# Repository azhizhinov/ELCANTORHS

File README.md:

## El Cantor HS

The El Cantor HS keyboard is a 44 key diodeless split keyboard with support for hotswap sockets, designed with simplicity in mind. It is based on the popular [cantor](https://github.com/diepala/cantor), which is inspired on the popular [corne](https://github.com/foostan/crkbd), [ferris](https://github.com/pierrechevalier83/ferris) and [sweep](https://github.com/davidphilipbarr/Sweep) keyboards, aiming to provide a more ergonomic (stronger column stagger) corne-like layout with a simple, easy to assemble and cheap design.
This is a WIP, you can follow the [Cantor's build guide](https://github.com/diepala/cantor/blob/main/doc/build_guide.md), as it is quite similar!

## Thanks
Big thanks to [@Excellenze11](https://github.com/Excellenze11) for ideas, cooperation and tests.

## Parts
As for the parts list, you will need:
- 2x PCB (The left and right half are the same)
- 44 Chocv1 Keys
- 44 Chocv1 Keycaps
- 44 Hotswap sockets for Chocv1 (optional)
- 2x TRRS jacks (PJ-320A)
- 2x Blackpill microcontrollers (STM32F401CC)

## Gerbers
You can find the Gerber files needed to order the PCB on the `Gerbers` directory. Look for the .zip of whatever version you would like!

## Firmware
Firmware for this keyboard is in the QMK tree. You can find sources in this [path](https://github.com/qmk/qmk_firmware/tree/master/keyboards/elcantorhs). You can see/change the layout [here](https://config.qmk.fm/#/elcantorhs/LAYOUT).

## Attention
I'm a hobbyist/amateur at best. So there may be things that aren't optimized. So if you decide to use this, then please be advised that I'm not providing any sort of liability and you should exercise some caution. Use these file for your own risk. Thanks Sebastian Stumpf for this text.

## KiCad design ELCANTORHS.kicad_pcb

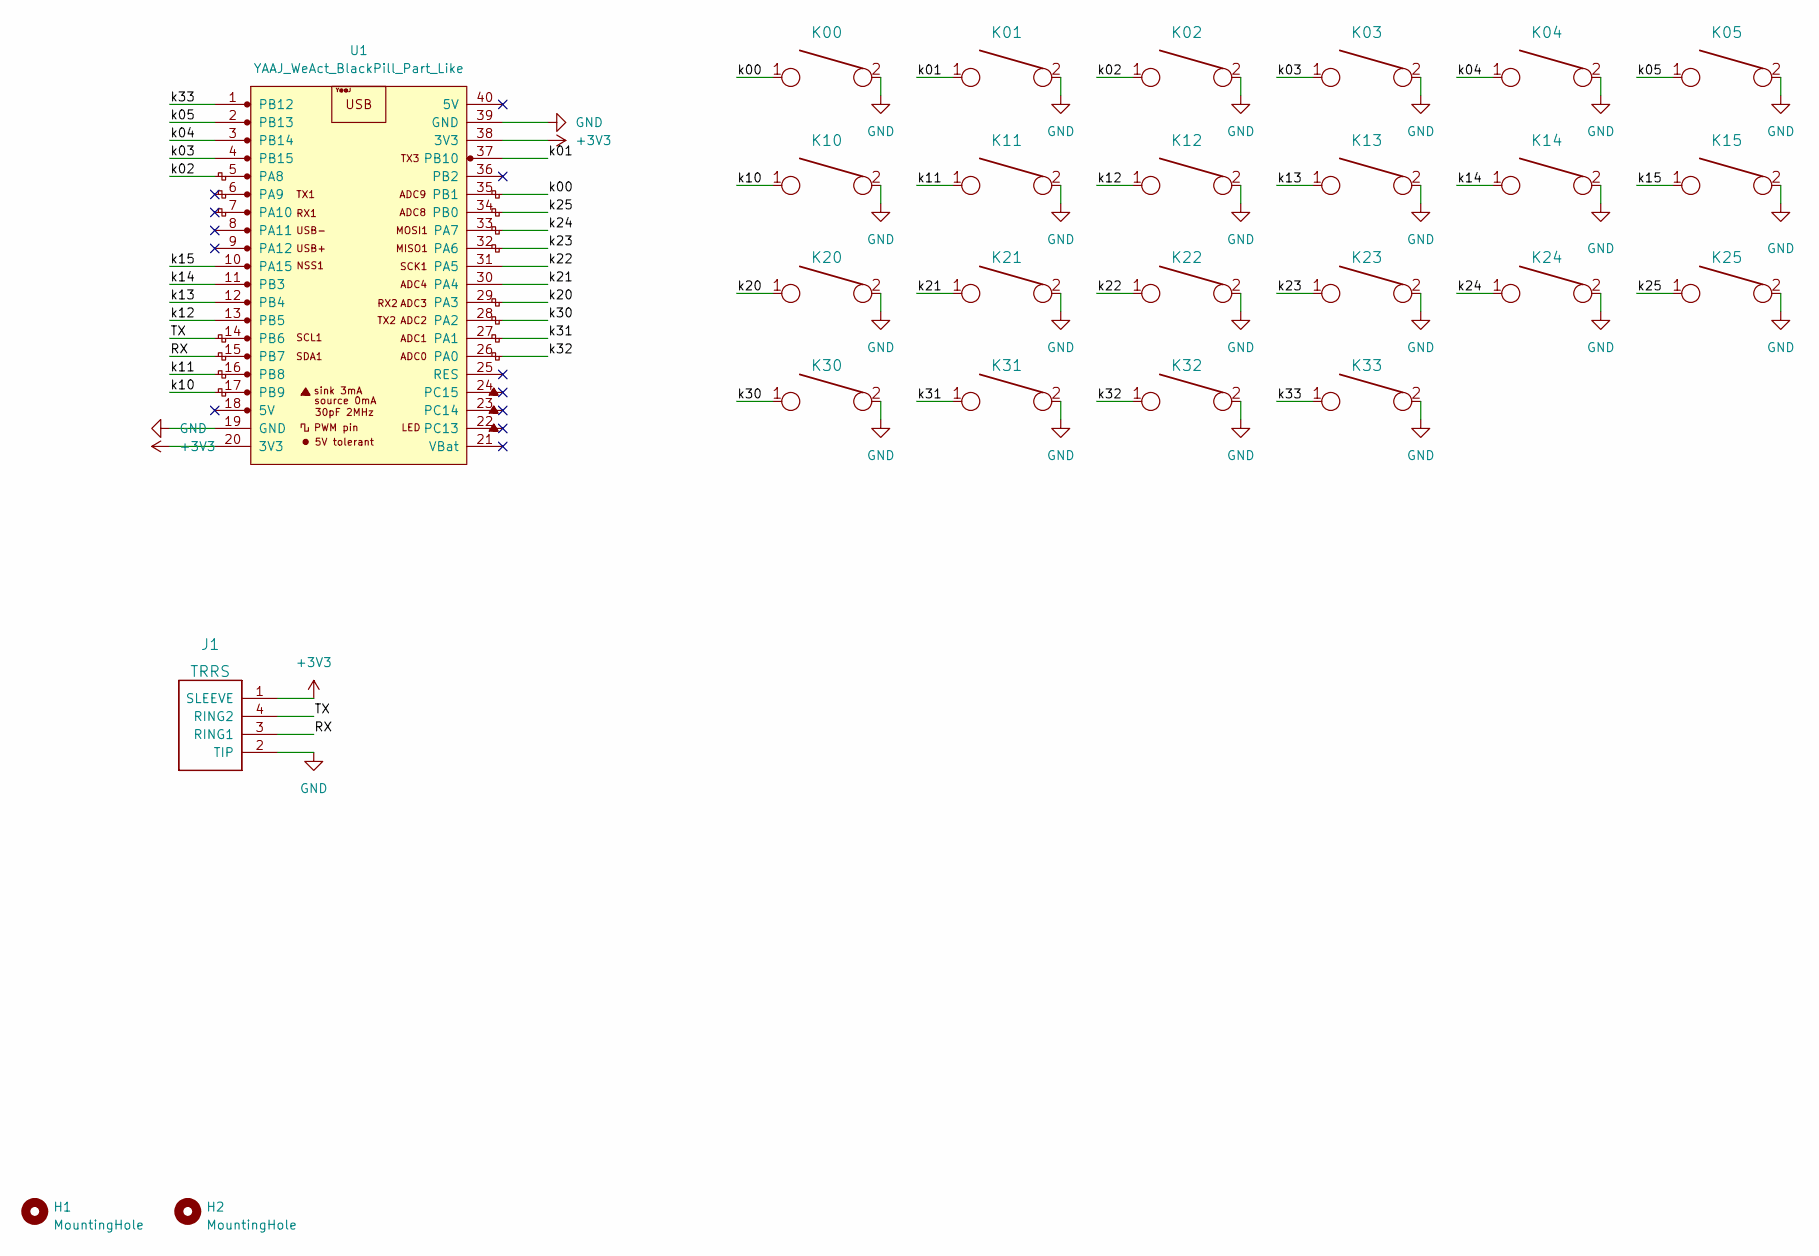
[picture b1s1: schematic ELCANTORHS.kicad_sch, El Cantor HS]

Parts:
H1, H2: MountingHole; breakaway-mousebites
J1: TRRS; TRRS-PJ-320A
K00, K01, K02, K03, K04, K05, K10, K11, K12, K13, K14, K15, K20, K21, K22, K23, K24, K25, K30, K31, K32, K33: KEYSW; Kailh_socket_PG1350_optional_reversible
U1: YAAJ_WeAct_BlackPill_Part_Like; YAAJ_WeAct_BlackPill_2

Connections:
+3V3: J1.1 (SLEEVE), U1.20 (3V3), U1.38 (3V3)
/RX: J1.3 (RING1), U1.15 (PB7)
/TX: J1.4 (RING2), U1.14 (PB6)
/k00: K00.1, U1.35 (PB1)
/k01: K01.1, U1.37 (PB10)
/k02: K02.1, U1.5 (PA8)
/k03: K03.1, U1.4 (PB15)
/k04: K04.1, U1.3 (PB14)
/k05: K05.1, U1.2 (PB13)
/k10: K10.1, U1.17 (PB9)
/k11: K11.1, U1.16 (PB8)
/k12: K12.1, U1.13 (PB5)
/k13: K13.1, U1.12 (PB4)
/k14: K14.1, U1.11 (PB3)
/k15: K15.1, U1.10 (PA15)
/k20: K20.1, U1.29 (PA3)
/k21: K21.1, U1.30 (PA4)
/k22: K22.1, U1.31 (PA5)
/k23: K23.1, U1.32 (PA6)
/k24: K24.1, U1.33 (PA7)
/k25: K25.1, U1.34 (PB0)
/k30: K30.1, U1.28 (PA2)
/k31: K31.1, U1.27 (PA1)
/k32: K32.1, U1.26 (PA0)
/k33: K33.1, U1.1 (PB12)
GND: J1.2 (TIP), K00.2, K01.2, K02.2, K03.2, K04.2, K05.2, K10.2, K11.2, K12.2, K13.2, K14.2, K15.2, K20.2, K21.2, K22.2, K23.2, K24.2, K25.2, K30.2, K31.2, K32.2, K33.2, U1.19 (GND), U1.39 (GND)

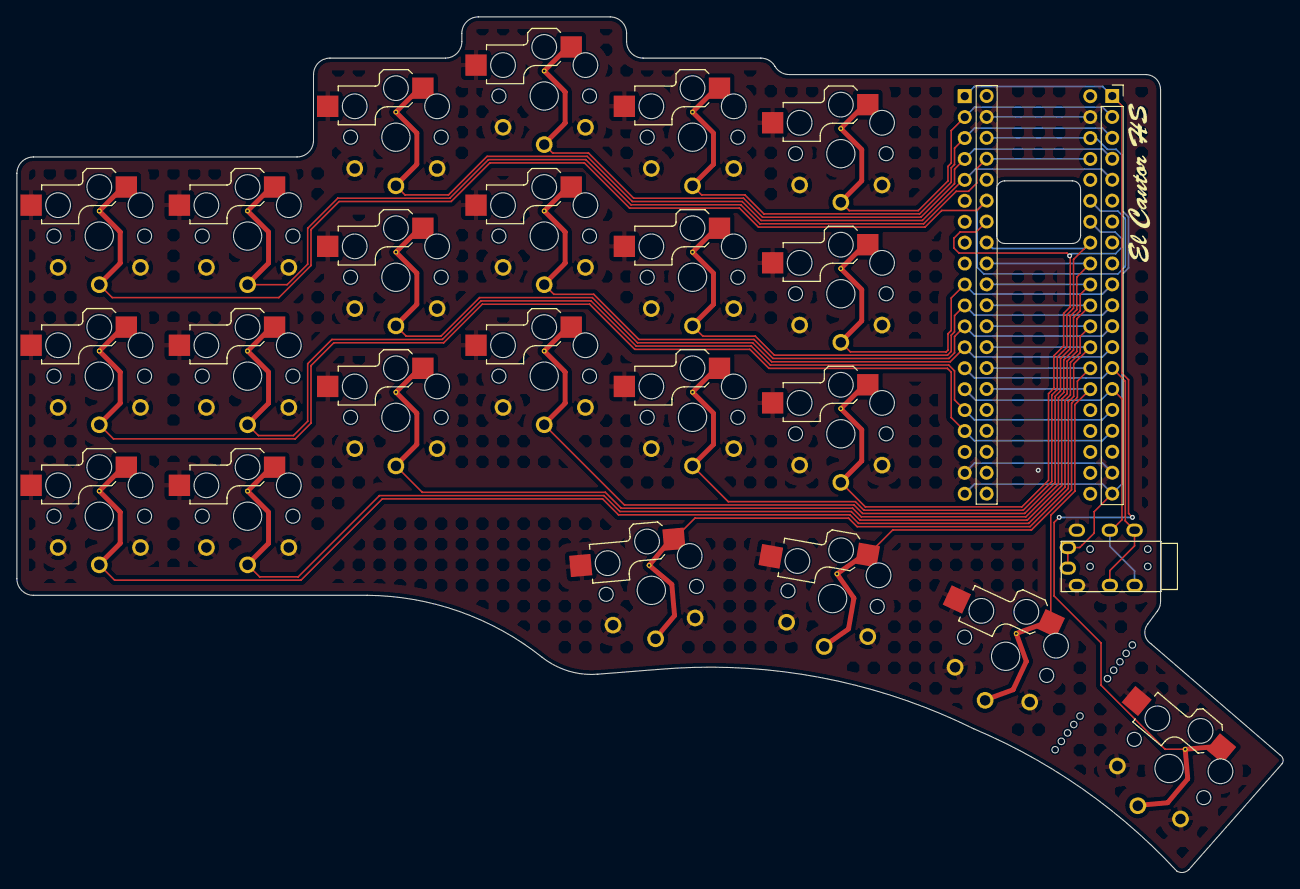
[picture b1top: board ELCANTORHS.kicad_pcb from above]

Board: 2 copper layers, 153.7 x 103.8 mm, 26 parts (0 on the bottom side), 26 nets.

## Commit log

2023-11-22 Initial upload.
2023-11-22 Adding pictures and gerbers.
2023-11-22 Adding the archive with gerbers.
